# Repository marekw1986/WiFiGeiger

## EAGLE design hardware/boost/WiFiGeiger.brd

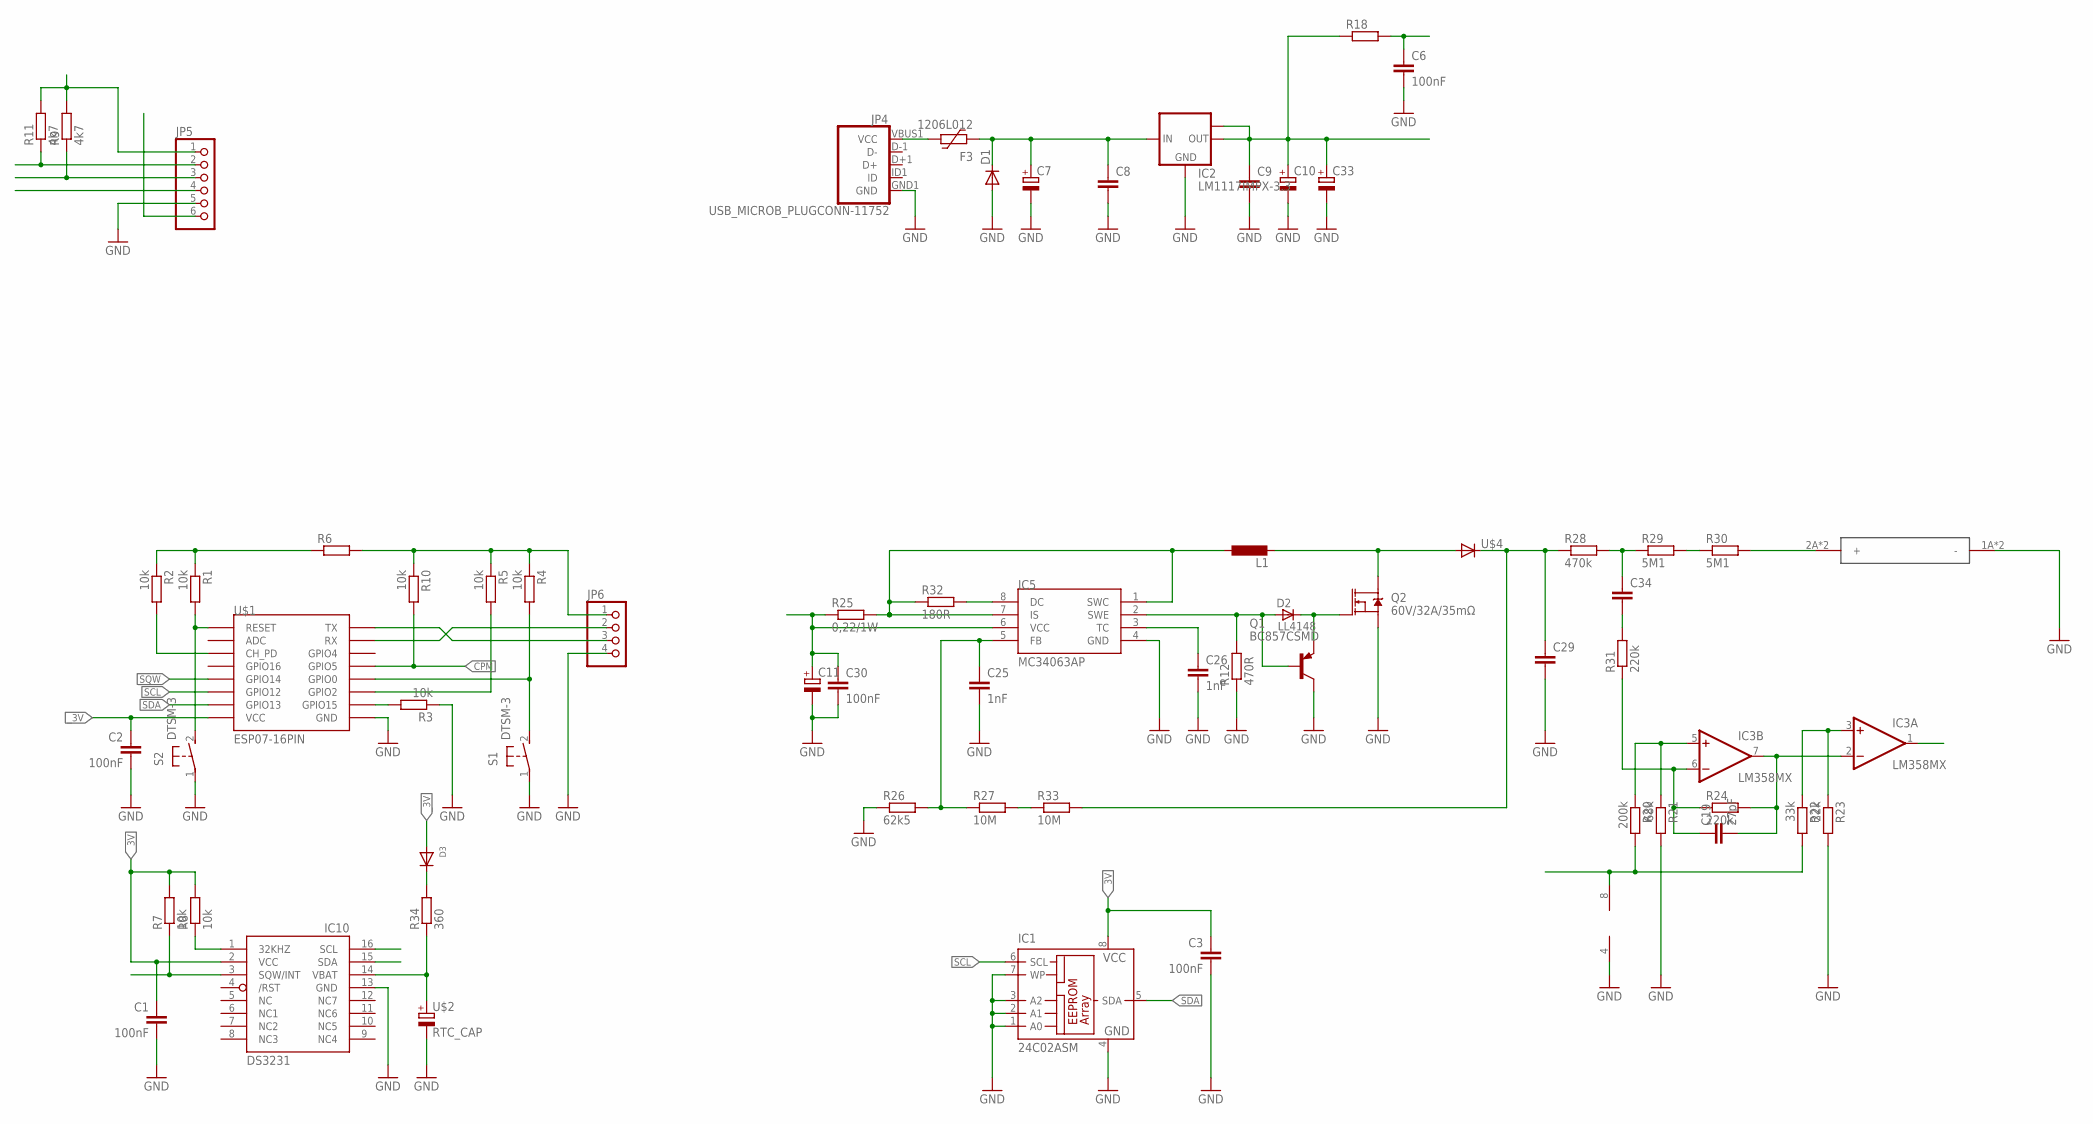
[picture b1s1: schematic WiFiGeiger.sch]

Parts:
C1, C2, C3, C6, C30: 100nF; C0603
C7, C10: CPOL-EUSMCC; SMC_C
C8, C9: C-EUC1206; C1206
C11: CPOL-EUSMCE; SMC_E
C19: 27pF; C0603
C25, C26: 1nF; C0603
C29: C-EU225-113X268; C225-113X268
C33: CPOL-EUSMCB; SMC_B
C34: C-EU050-024X044; C050-024X044
D1: DIODE-SMB; SMB
D2: LL4148; SOD80_DO213AA_MINIMELF
D3: DIODESMA; SMADIODE
F3: 1206L012; 1206L
IC1: 24C02ASM; SO-08M
IC2: LM1117IMPX-3.3; SOT223
IC3: LM358MX; SO08
IC5: MC34063AP; DIL08
IC10: DS3231/SO; SO16W
JP4: USB_MICROB_PLUGCONN-11752; USB-B-MICRO-SMD_V03
JP5: PINHD-1X6; 1X06
JP6: PINHD-1X4; 1X04
L1: L-EU6000-XXX-RC; 6000-XXXX-RC
Q1: BC857CSMD; SOT23-BEC
Q2: 60V/32A/35mΩ; TO220V
R1, R2, R3, R4, R5, R7, R8, R10: 10k; R0603
R6: R-EU_R2010; R2010
R9, R11: 4k7; R0603
R12: 470R; R1206
R18: R-EU_R1206; R1206
R20: 200k; R0603
R21: 68k; R0603
R22: 33k; R1206
R23: 22k; R0603
R24: 220k; R0603
R25: 0,22/1W; R2010
R26: 62k5; R1206
R27, R33: 10M; R2512
R28: 470k; R2512
R29, R30: 5M1; R2512
R31: 220k; R0805
R32: 180R; R0805
R34: 360; R0603
S1, S2: DTSM-3
U$1: ESP07-16PIN
U$2: RTC_CAP
U$4: DIODE-MELF-MLL41; MELF-MLL41
U$5: STS5; GEIGERTUBE

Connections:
3V: JP6.1, R4.1, R5.1, R6.2, R10.1
A_3V: C6.1, IC3.8 (V+), R18.2, R20.2, R22.2
CPM: IC3.1 (OUT), R10.2, U$1.GPIO5
GND: C1.2, C2.2, C3.2, C6.2, C7.-, C8.2, C9.2, C10.-, C11.-, C25.2, C26.2, C29.2, C30.2, C33.-, D1.A, IC1.1 (A0), IC1.2 (A1), IC1.3 (A2), IC1.4 (GND), IC1.7 (WP), IC2.1 (GND), IC3.4 (V-), IC5.4 (GND), IC10.13 (GND), JP4.GND1 (GND), JP5.5, JP6.4, Q1.C, Q2.3 (S), R3.1, R12.1, R21.2, R23.2, R26.1, S1.1, S2.1, U$1.GND, U$2.P$2 (-), U$5.1A (-), U$5.1B (-)
HV: C29.1, R28.1, R33.2, U$4.C
IO_INT: JP5.4
unnamed: R1.2, S2.2, U$1.REST (RESET)
unnamed: R2.2, U$1.CH_PD
unnamed: D2.A, IC5.2 (SWE), Q1.B, R12.2
unnamed: C19.1, IC3.6 (-IN), R24.1, R31.1
unnamed: R3.2, U$1.GPIO15
unnamed: R4.2, S1.2, U$1.GPIO0
unnamed: C19.2, IC3.2 (-IN), IC3.7 (OUT), R24.2
unnamed: R5.2, U$1.GPIO2
unnamed: C26.1, IC5.3 (TC)
unnamed: IC10.14 (VBAT), R34.1, U$2.P$1 (+)
unnamed: IC10.1 (32KHZ), R8.1
unnamed: F3.1, JP4.VBUS1 (VCC)
unnamed: JP6.3, U$1.TX
unnamed: IC5.1 (SWC), IC5.7 (IS), L1.1, R25.2, R32.1
unnamed: D3.C, R34.2
unnamed: IC3.5 (+IN), R20.1, R21.1
unnamed: IC3.3 (+IN), R22.1, R23.1
unnamed: L1.2, Q2.2 (D), U$4.A
unnamed: D2.C, Q1.E, Q2.1 (G)
unnamed: JP6.2, U$1.RX
unnamed: C25.1, IC5.5 (FB), R26.2, R27.1
unnamed: R30.2, U$5.2A (+), U$5.2B (+)
unnamed: R29.2, R30.1
unnamed: C34.1, R28.2, R29.1
unnamed: C34.2, R31.2
unnamed: IC5.8 (DC), R32.2
unnamed: R27.2, R33.1
SCL: IC1.6 (SCL), IC10.16 (SCL), JP5.3, R9.1, U$1.GPIO12
SDA: IC1.5 (SDA), IC10.15 (SDA), JP5.2, R11.1, U$1.GPIO13
SQW: IC10.3 (SQW/INT), R7.1, U$1.GPIO14
VBUS: C7.+, C8.1, C11.+, C30.1, D1.C, F3.2, IC2.3 (IN), IC5.6 (VCC), JP5.6, R25.1
_3V: C1.1, C2.1, C3.1, C9.1, C10.+, C33.+, D3.A, IC1.8 (VCC), IC2.2 (OUT), IC2.TAB (OUT1), IC10.2 (VCC), JP5.1, R1.1, R2.1, R6.1, R7.2, R8.2, R9.2, R11.2, R18.1, U$1.VCC

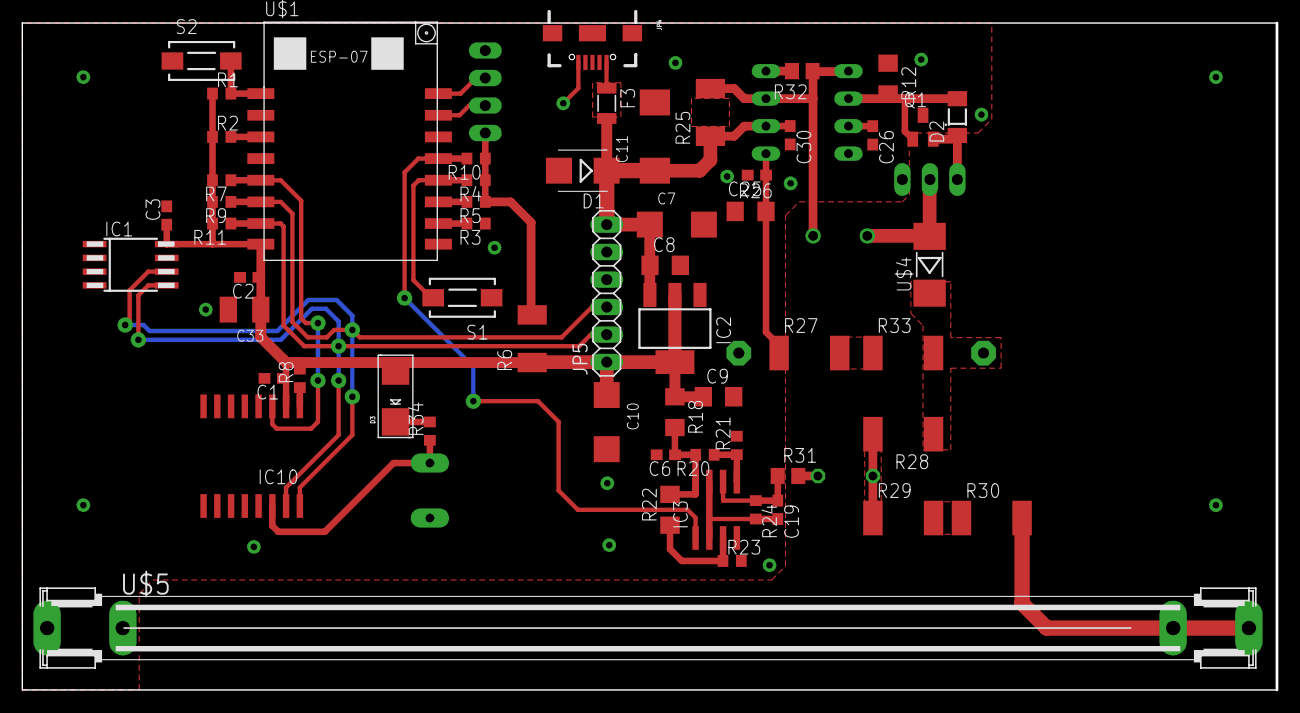
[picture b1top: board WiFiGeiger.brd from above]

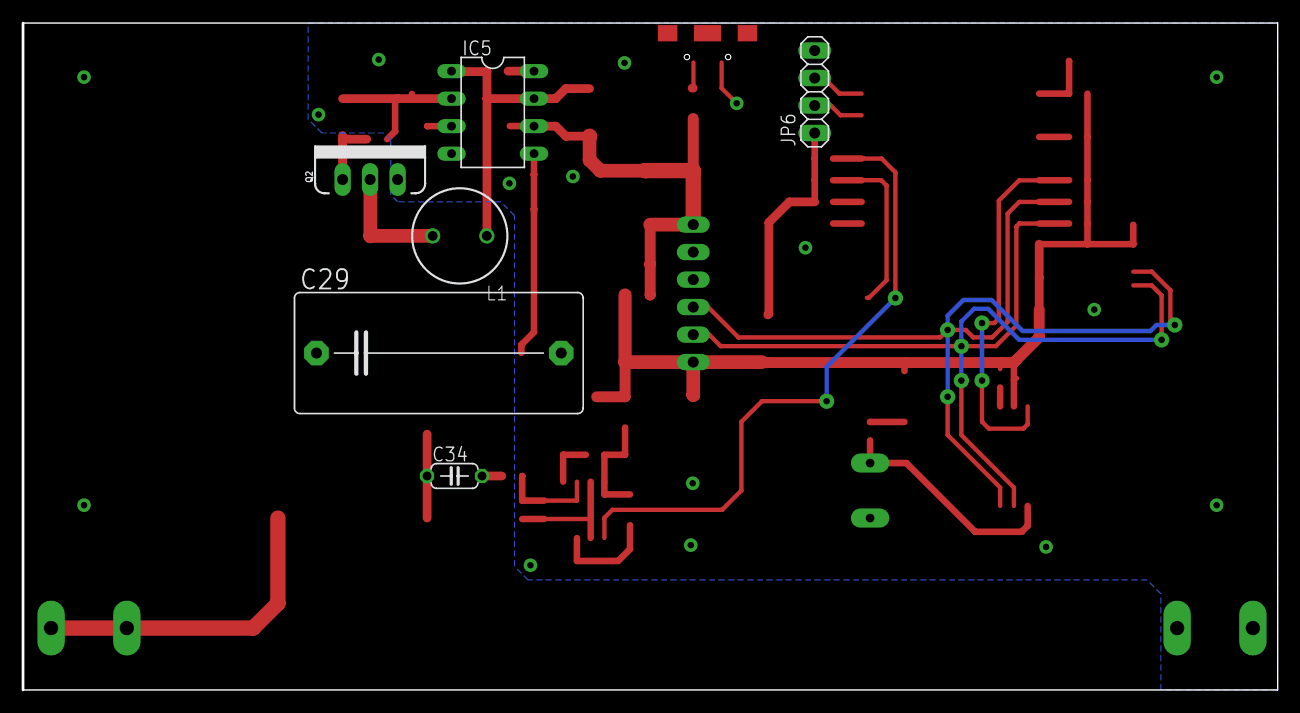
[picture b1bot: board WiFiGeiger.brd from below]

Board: 2 copper layers, 115.9 x 61.6 mm, 65 parts (6 on the bottom side), 37 nets.

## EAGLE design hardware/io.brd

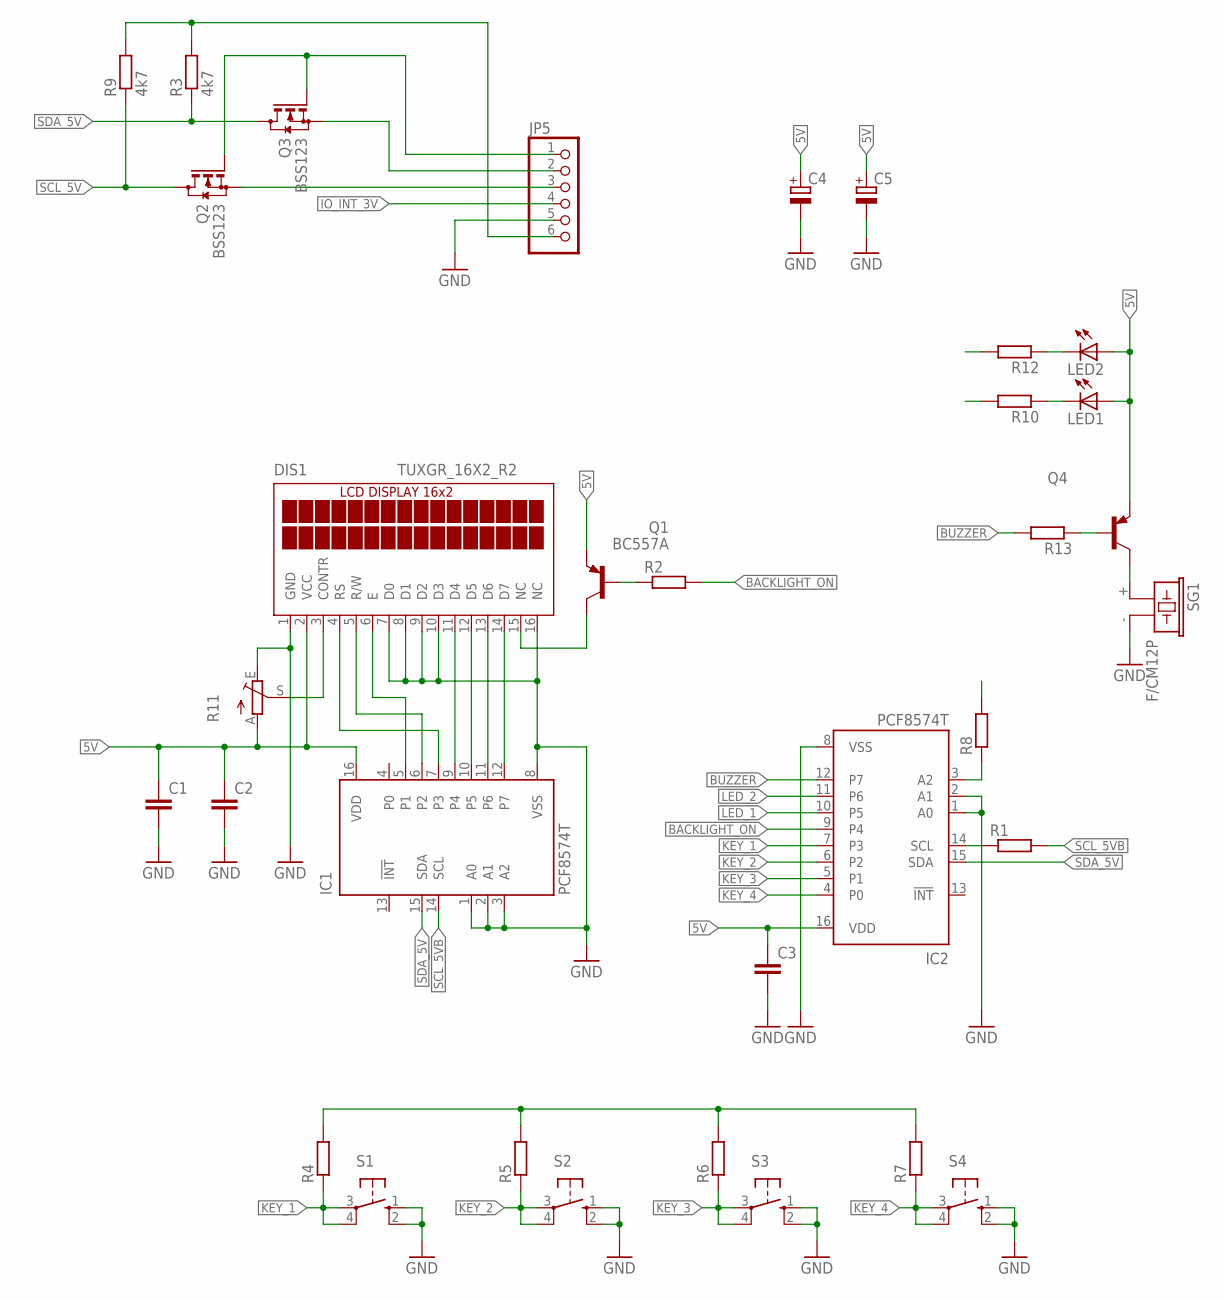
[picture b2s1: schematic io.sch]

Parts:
C1, C3: C-EUC1206; C1206
C2: C-EUC0603; C0603
C4, C5: CPOL-EUSMCD; SMC_D
DIS1: TUXGR_16X2_R2
IC1, IC2: PCF8574T; SO16W
JP5: PINHD-1X6; 1X06
LED1, LED2: LED5MM
Q1: BC557A; TO92-EBC
Q2, Q3: BSS123; SOT23
Q4: BC557A-PNP-TO92-EBC; TO92-EBC
R1, R8, R13: R-EU_R0603; R0603
R2, R6, R7, R10, R12: R-EU_0204/5; 0204/5
R3: 4k7; R0603
R4, R5: R-EU_0204/7; 0204/7
R9: 4k7; R1206
R11: TRIM_EU-B25U; B25U
S1, S2, S3, S4: 10-XX; B3F-10XX
SG1: F/CM12P

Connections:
5V: C1.1, C2.1, C3.1, C4.+, C5.+, DIS1.2 (VCC), IC1.16 (VDD), IC2.16 (VDD), JP5.6, LED1.A, LED2.A, Q1.E, Q4.E, R3.2, R4.2, R5.2, R6.2, R7.2, R8.2, R9.2, R11.A
BACKLIGHT_ON: IC2.9 (P4), R2.2
BUZZER: IC2.12 (P7), R13.2
GND: C1.2, C2.2, C3.2, C4.-, C5.-, DIS1.1 (GND), DIS1.7 (D0), DIS1.8 (D1), DIS1.9 (D2), DIS1.10 (D3), DIS1.16 (NC), IC1.1 (A0), IC1.2 (A1), IC1.3 (A2), IC1.8 (VSS), IC2.1 (A0), IC2.2 (A1), IC2.8 (VSS), JP5.5, R11.E, S1.1 (S), S1.2 (S1), S2.1 (S), S2.2 (S1), S3.1 (S), S3.2 (S1), S4.1 (S), S4.2 (S1), SG1.- (2)
IO_INT_3V: JP5.4
KEY_1: IC2.7 (P3), R4.1, S1.3, S1.4 (P1)
KEY_2: IC2.6 (P2), R5.1, S2.3, S2.4 (P1)
KEY_3: IC2.5 (P1), R6.1, S3.3, S3.4 (P1)
KEY_4: IC2.4 (P0), R7.1, S4.3, S4.4 (P1)
LED_1: IC2.10 (P5), R10.2
LED_2: IC2.11 (P6), R12.2
unnamed: DIS1.14 (D7), IC1.12 (P7)
unnamed: DIS1.13 (D6), IC1.11 (P6)
unnamed: DIS1.12 (D5), IC1.10 (P5)
unnamed: DIS1.11 (D4), IC1.9 (P4)
unnamed: DIS1.6 (E), IC1.5 (P1)
unnamed: DIS1.5 (R/W), IC1.6 (P2)
unnamed: DIS1.4 (RS), IC1.7 (P3)
unnamed: IC2.3 (A2), R8.1
unnamed: DIS1.15 (NC), Q1.C
unnamed: Q1.B, R2.1
unnamed: DIS1.3 (CONTR), R11.S
unnamed: LED1.K (C), R10.1
unnamed: LED2.K (C), R12.1
unnamed: Q4.C, SG1.+ (1)
unnamed: Q4.B, R13.1
SCL_3V: JP5.3, Q2.2 (S)
SCL_5V: IC2.14 (SCL), Q2.3 (D), R1.1, R9.1
SCL_5VB: IC1.14 (SCL), R1.2
SDA_3V: JP5.2, Q3.2 (S)
SDA_5V: IC1.15 (SDA), IC2.15 (SDA), Q3.3 (D), R3.1
_3V: JP5.1, Q2.1 (G), Q3.1 (G)

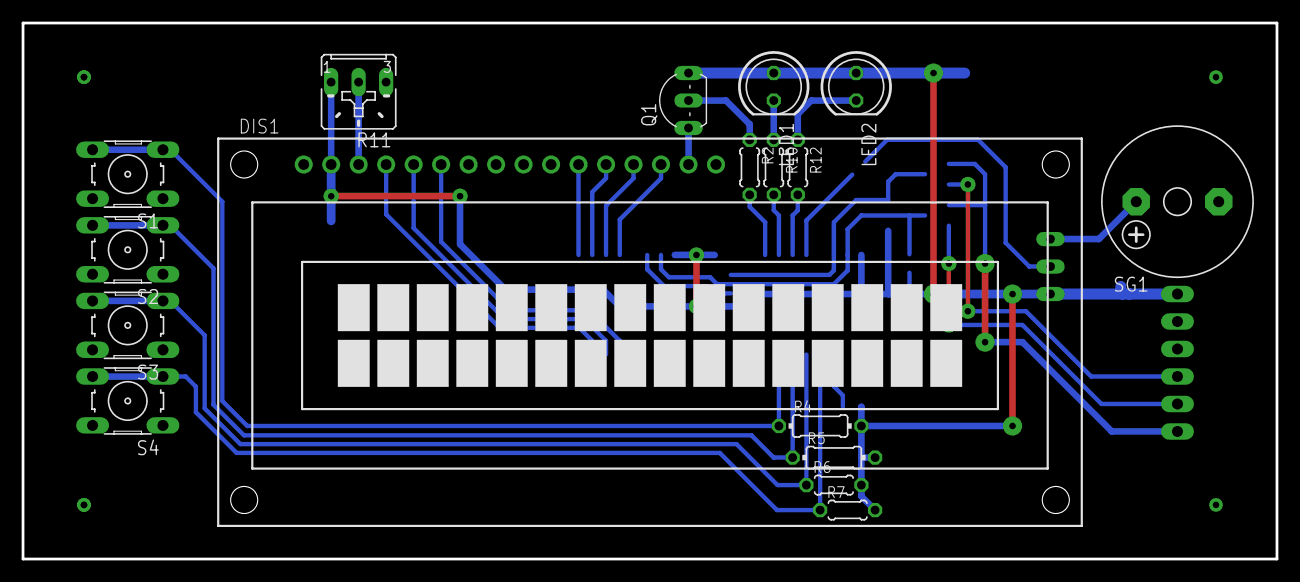
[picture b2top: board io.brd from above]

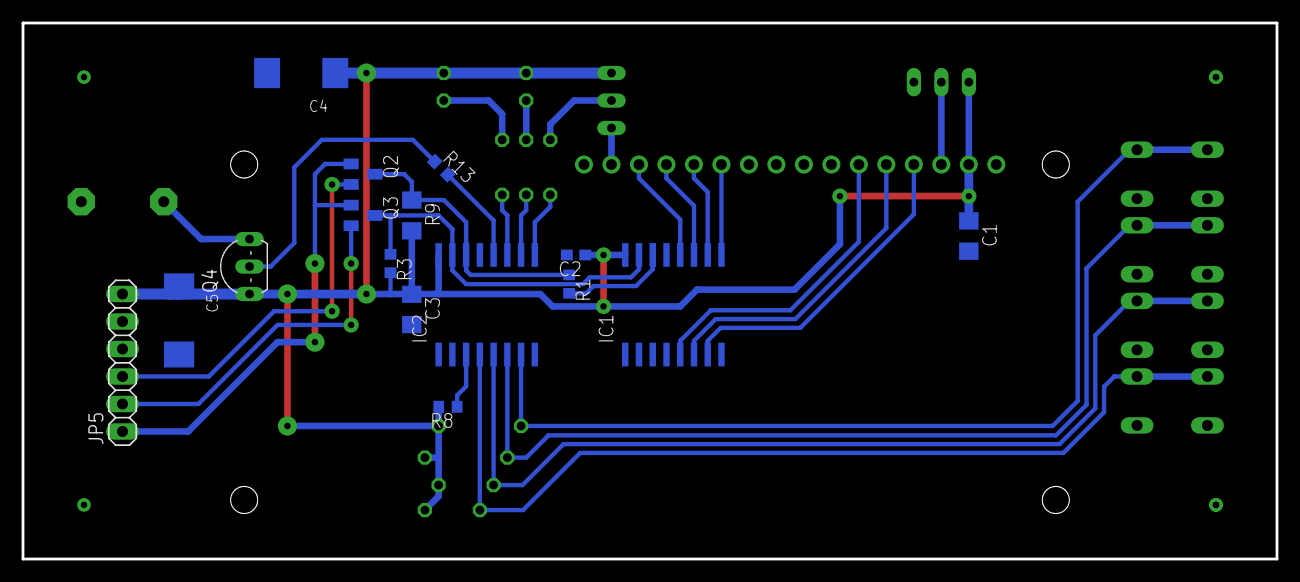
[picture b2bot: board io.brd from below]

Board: 2 copper layers, 115.9 x 49.5 mm, 33 parts (16 on the bottom side), 31 nets.

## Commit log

2021-03-11 Some changes
2021-03-11 Testing
2021-03-20 Geiger counter
2021-03-24 HTTP and JSON
2022-05-26 MQTT
2022-05-30 Sysinfo added
2022-05-31 common.c and common.h created
2022-05-31 SPIFS added
2022-05-31 some possible memory leaks avoided
2022-06-02 webinterface
2022-06-03 minor changes
2022-06-03 jquery added
2022-06-04 webinterface modified
2022-06-08 mallocs fixed
2022-06-08 config added
2022-06-08 hardreset
2022-06-08 reset from webui
2022-06-08 change password
2022-06-09 valiiting ip and password
2022-06-09 parsing config
2022-06-09 config parser
2022-06-09 config
2022-06-13 scanning wifi
2022-06-13 some chages
2022-06-13 i2c rtc
2022-06-14 minor changes in rtc
2022-06-14 wifi fixes
2022-06-17 basic authentication added
2022-06-20 softAP
2022-06-20 button
2022-06-22 minor change
2022-06-23 connect to wifi frm webui
2022-07-03 reconnect in runtime works
2022-07-04 starting HTTPD with AP
2022-07-06 ipconfig
2022-07-06 ip fixes
2022-07-06 semaphores protecting configuration
2022-07-07 strtok_r instead strtok
2022-07-08 MQTT client logs time of last message
2022-07-08 reporting mqtt connection status
2022-07-10 additional uri
2022-07-10 last mqtt log shown at status page
2022-07-12 configurable MQTT
2022-07-15 Reconfiguring MQTT after config change
2022-07-27 bme280 added
2022-07-28 Semaphore protecting BME data
2022-07-28 fixes
2022-08-05 minor fix
2022-08-07 mqtt fix
2022-12-06 Boost version of hardware added

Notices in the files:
parts and their libraries:
SparkFun-Connectors: Licensing: Creative Commons ShareAlike 4.0 International - https://creativecommons.org/licenses/by-sa/4.0
